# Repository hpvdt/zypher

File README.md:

# Zypher
Code and CAD of our 2019 ASME electronics system. Electronics hardware was designed in EAGLE, microcontroller code was prepared using the Arduino IDE. A mobile app prepared in MIT App Inventer 2 was used as the primary user interface.

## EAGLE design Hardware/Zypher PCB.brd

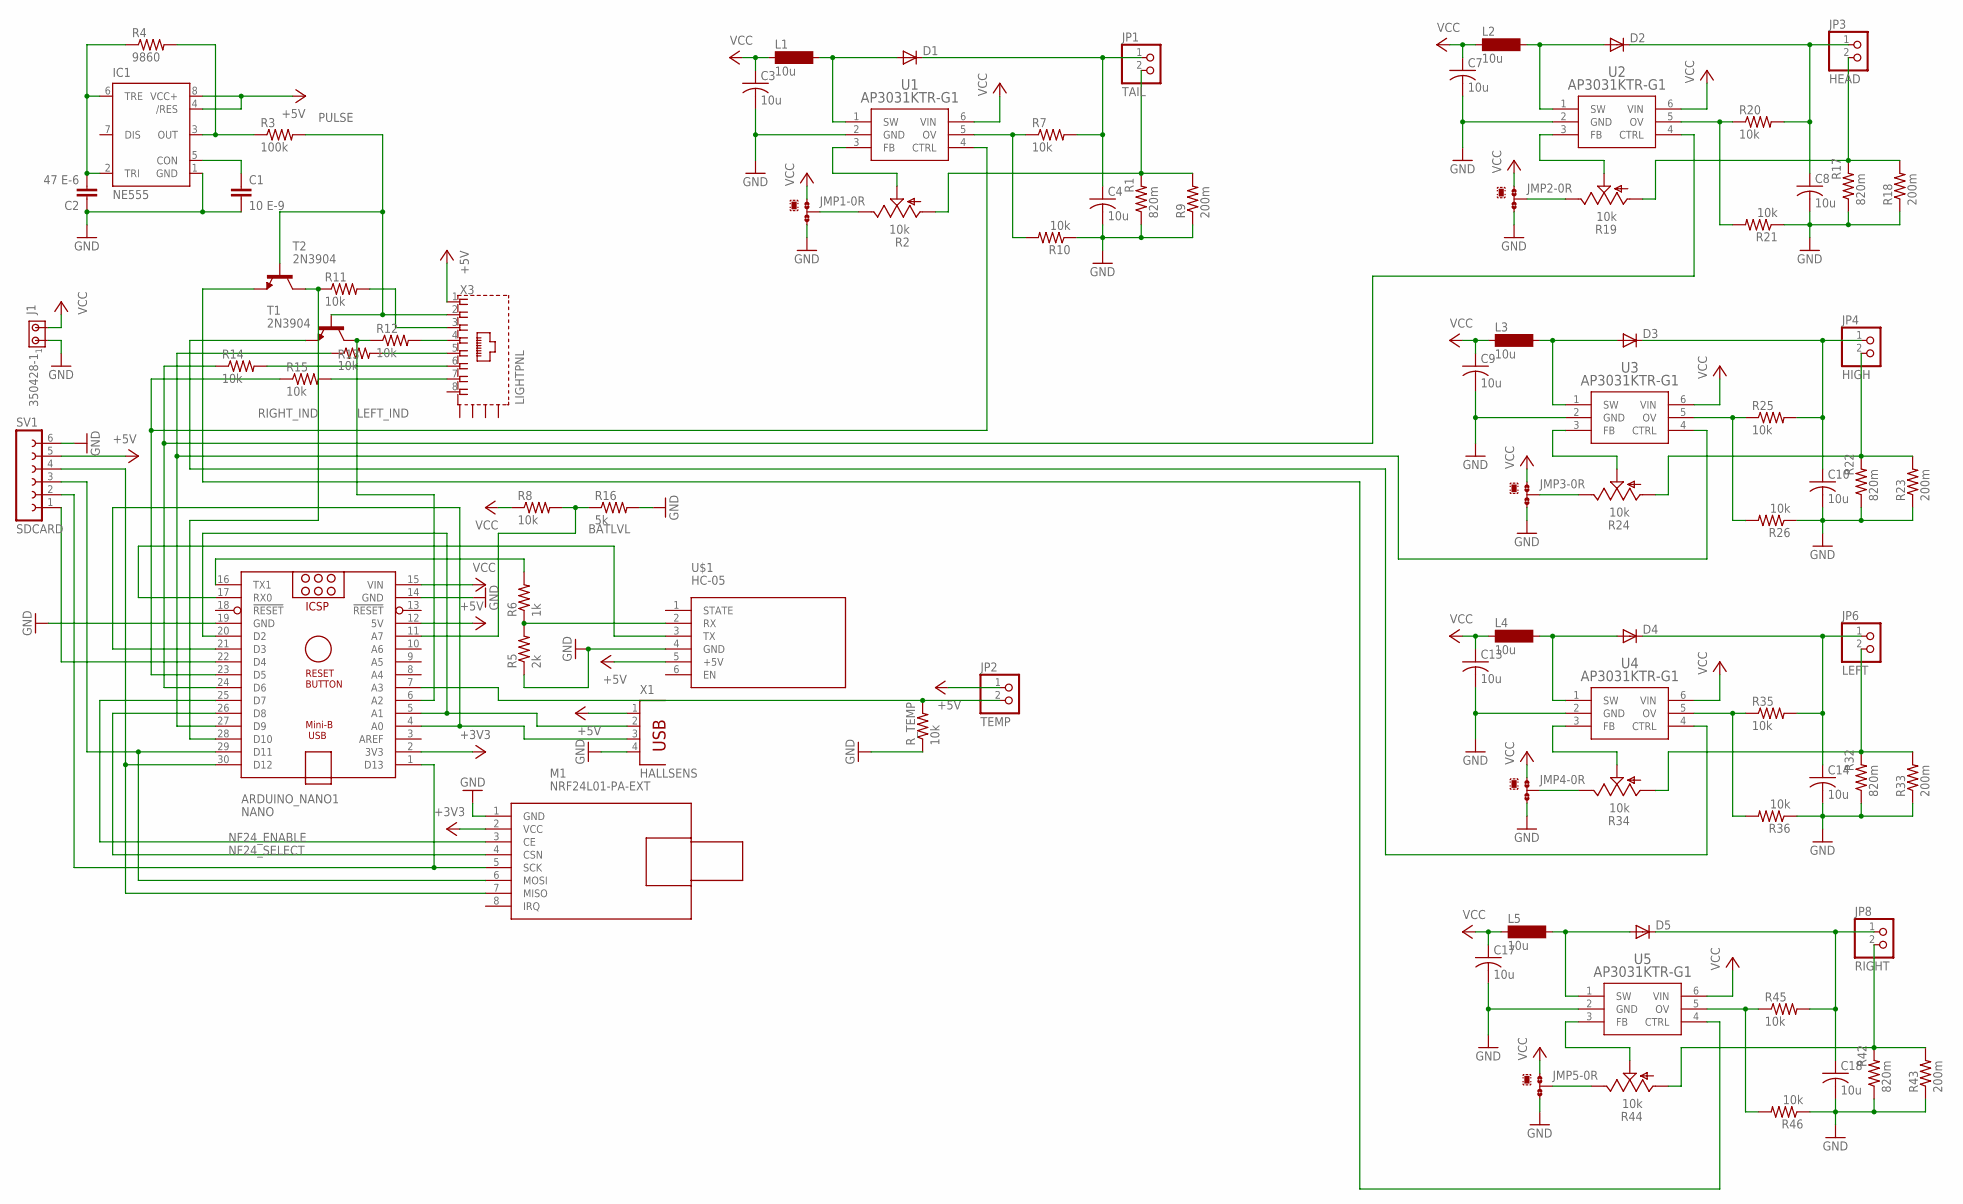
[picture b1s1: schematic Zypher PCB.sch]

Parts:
ARDUINO_NANO1: NANO; ARDUINO_NANO
C1: 10 E-9; C2.5-5
C2: 47 E-6; C2.5-5
C3, C4, C7, C8, C9, C10, C13, C14, C17, C18: 10u; C1206K
D1, D2, D3, D4, D5: DIODE-DO-214AC; DO-214AC
IC1: NE555; DIL-08
J1: 350428-1
JMP1, JMP2, JMP3, JMP4, JMP5: 0R-JUMPA; A0R-JMP
JP1: TAIL; 1X02
JP2: TEMP; 1X02
JP3: HEAD; 1X02
JP4: HIGH; 1X02
JP6: LEFT; 1X02
JP8: RIGHT; 1X02
L1, L2, L3, L4, L5: 10u; SD12K100
M1: NRF24L01-PA-EXT; WIRELESS-NRF24L01-PA-EXT
R1, R17, R22, R32, R42: 820m; R0603
R2, R19, R24, R34, R44: 10k; RJ9W
R3: 100k; 0207/7
R4: 9860; 0207/7
R5: 2k; 0204/7
R6: 1k; 0204/7
R7, R10, R20, R21, R25, R26, R35, R36, R45, R46: 10k; 0207/2V
R8, R11, R12, R13, R14, R15: 10k; 0207/7
R9, R18, R23, R33, R43: 200m; R0805
R16: 5k; 0207/7
R_TEMP: 10k; 0207/7
SV1: SDCARD; FE06W
T1, T2: 2N3904; TO92
U1, U2, U3, U4, U5: AP3031KTR-G1; SOT23-6
U$1: HC-05; WIRELESS-BLUETOOTH-HC-05
X1: HALLSENS; PN87520
X3: LIGHTPNL; RJ45-SHIELD1

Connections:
+3V3: ARDUINO_NANO1.2 (3V3), M1.2 (VCC)
+5V: ARDUINO_NANO1.12 (5V), IC1.4 (/RES), IC1.8 (VCC+), JP2.1, SV1.5, U$1.5 (+5V), X1.1, X3.1
BATLVL: ARDUINO_NANO1.11 (A7), R8.2, R16.1
CLK: ARDUINO_NANO1.1 (D13), M1.5 (SCK), SV1.2
GND: ARDUINO_NANO1.14 (GND), ARDUINO_NANO1.19 (GND), C1.2, C2.1, C3.2, C4.2, C7.2, C8.2, C9.2, C10.2, C13.2, C14.2, C17.2, C18.2, IC1.1 (GND), J1.1, JMP1.3, JMP2.3, JMP3.3, JMP4.3, JMP5.3, M1.1 (GND), R1.1, R5.1, R9.1, R10.1, R16.2, R17.1, R18.1, R21.1, R22.1, R23.1, R26.1, R32.1, R33.1, R36.1, R42.1, R43.1, R46.1, R_TEMP.1, SV1.6, U1.2 (GND), U2.2 (GND), U3.2 (GND), U4.2 (GND), U5.2 (GND), U$1.4 (GND), X1.4
HALL1: ARDUINO_NANO1.4 (A0), ARDUINO_NANO1.21 (D3), X1.3
HALL2: ARDUINO_NANO1.5 (A1), ARDUINO_NANO1.20 (D2), X1.2
HEAD_CTRL: ARDUINO_NANO1.24 (D6), R14.1, U2.4 (CTRL)
HIGH_CTRL: ARDUINO_NANO1.27 (D9), R13.1, U3.4 (CTRL)
LEFT+: C14.1, D4.C, JP6.1, R35.2
LEFT-: JP6.2, R32.2, R33.2, R34.A
LEFT_CTRL: T1.3 (E), U4.4 (CTRL)
LEFT_IND: ARDUINO_NANO1.6 (A2), R12.1, T1.1 (C)
MISO: ARDUINO_NANO1.30 (D12), M1.7 (MISO), SV1.4
MOSI: ARDUINO_NANO1.29 (D11), M1.6 (MOSI), SV1.3
unnamed: D1.A, L1.2, U1.1 (SW)
unnamed: C1.1, IC1.5 (CON)
unnamed: C4.1, D1.C, JP1.1, R7.2
unnamed: C2.2, IC1.2 (TRI), IC1.6 (TRE), R4.1
unnamed: IC1.3 (OUT), R3.1, R4.2
unnamed: R2.S, U1.3 (FB)
unnamed: JP1.2, R1.2, R2.A, R9.2
unnamed: JMP1.2, R2.E
unnamed: R5.2, R6.1, U$1.2 (RX)
unnamed: R7.1, R10.2, U1.5 (OV)
unnamed: R14.2, X3.6
unnamed: R13.2, X3.5
unnamed: R11.2, X3.3
unnamed: R12.2, X3.4
unnamed: R15.2, X3.7
unnamed: D2.A, L2.2, U2.1 (SW)
unnamed: C8.1, D2.C, JP3.1, R20.2
unnamed: JP3.2, R17.2, R18.2, R19.A
unnamed: R19.S, U2.3 (FB)
unnamed: JMP2.2, R19.E
unnamed: R20.1, R21.2, U2.5 (OV)
unnamed: D3.A, L3.2, U3.1 (SW)
unnamed: C10.1, D3.C, JP4.1, R25.2
unnamed: JP4.2, R22.2, R23.2, R24.A
unnamed: R24.S, U3.3 (FB)
unnamed: JMP3.2, R24.E
unnamed: R25.1, R26.2, U3.5 (OV)
unnamed: D4.A, L4.2, U4.1 (SW)
unnamed: R34.S, U4.3 (FB)
unnamed: JMP4.2, R34.E
unnamed: R35.1, R36.2, U4.5 (OV)
unnamed: D5.A, L5.2, U5.1 (SW)
unnamed: R44.S, U5.3 (FB)
unnamed: JMP5.2, R44.E
unnamed: R45.1, R46.2, U5.5 (OV)
NF24_ENABLE: ARDUINO_NANO1.25 (D7), M1.3 (CE)
NF24_SELECT: ARDUINO_NANO1.26 (D8), M1.4 (CSN)
PULSE: R3.2, T1.2 (B), T2.2 (B), X3.2
RIGHT+: C18.1, D5.C, JP8.1, R45.2
RIGHT-: JP8.2, R42.2, R43.2, R44.A
RIGHT_CTRL: T2.3 (E), U5.4 (CTRL)
RIGHT_IND: ARDUINO_NANO1.28 (D10), R11.1, T2.1 (C)
RX: ARDUINO_NANO1.17 (RX0), U$1.3 (TX)
SD_SEL: ARDUINO_NANO1.22 (D4), SV1.1
TAIL_CTRL: ARDUINO_NANO1.23 (D5), R15.1, U1.4 (CTRL)
TEMP: ARDUINO_NANO1.7 (A3), JP2.2, R_TEMP.2
TX: ARDUINO_NANO1.16 (TX1), R6.2
VCC: ARDUINO_NANO1.15 (VIN), C3.1, C7.1, C9.1, C13.1, C17.1, J1.2, JMP1.1, JMP2.1, JMP3.1, JMP4.1, JMP5.1, L1.1, L2.1, L3.1, L4.1, L5.1, R8.1, U1.6 (VIN), U2.6 (VIN), U3.6 (VIN), U4.6 (VIN), U5.6 (VIN)

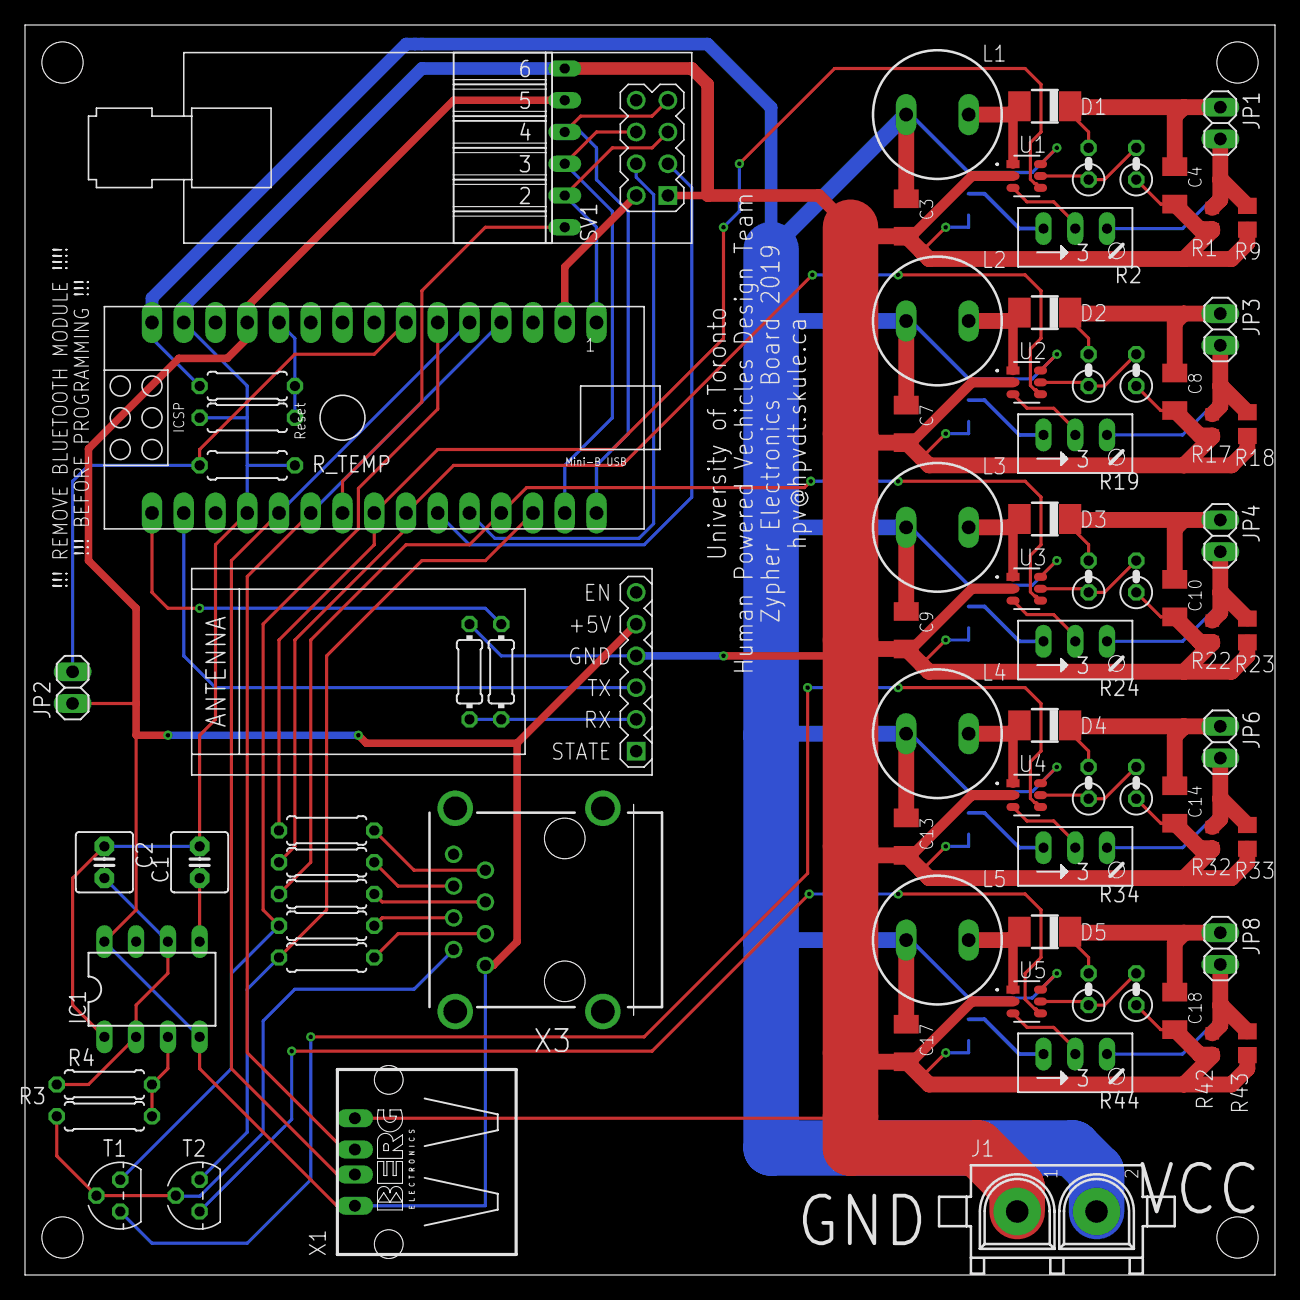
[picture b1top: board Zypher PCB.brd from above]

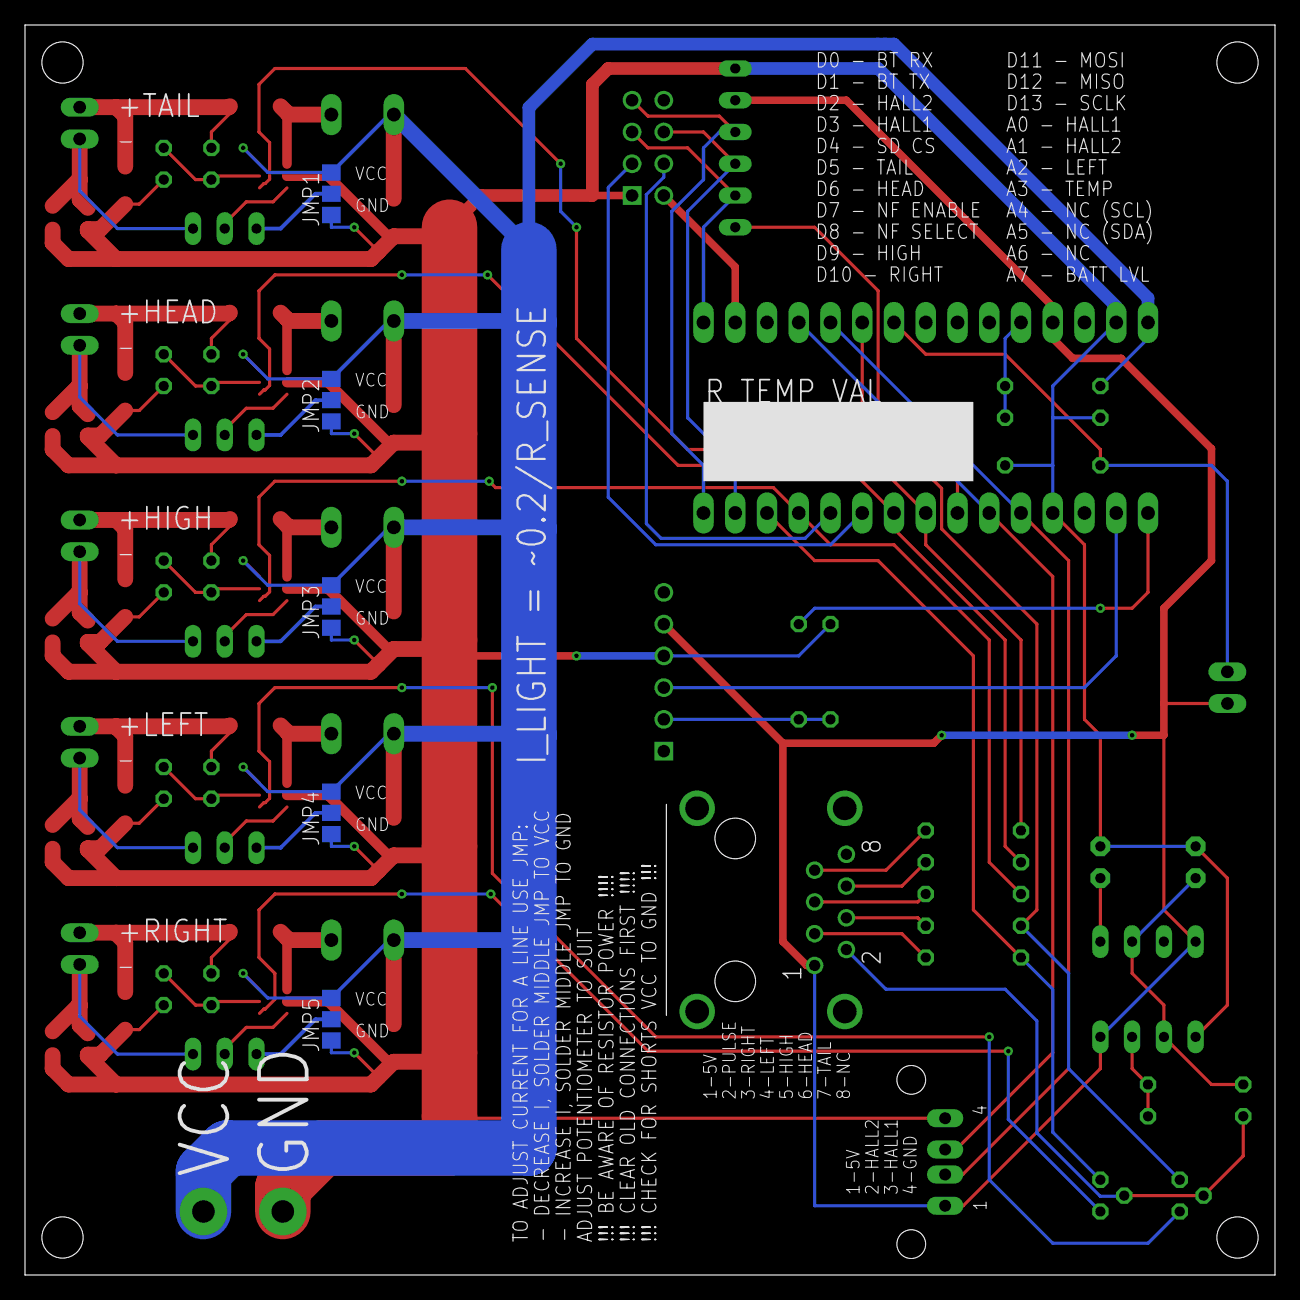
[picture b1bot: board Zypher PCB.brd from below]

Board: 2 copper layers, 100.0 x 100.0 mm, 85 parts (5 on the bottom side), 63 nets.

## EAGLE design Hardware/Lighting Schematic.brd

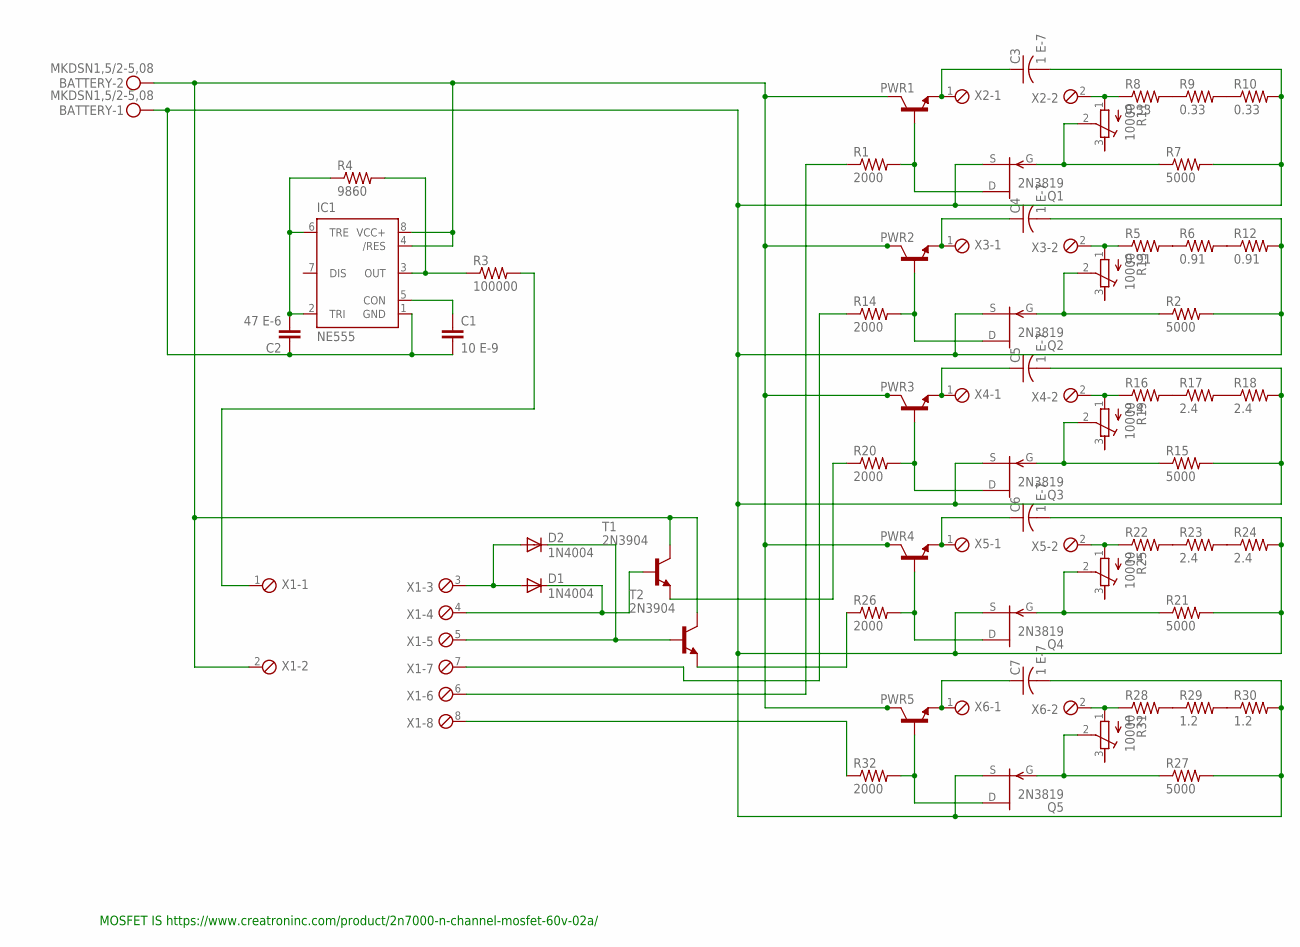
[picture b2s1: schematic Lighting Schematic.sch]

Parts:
BATTERY: MKDSN1,5/2-5,08
C1: 10 E-9; C2.5-5
C2: 47 E-6; C2.5-5
C3, C4, C5, C6, C7: 1 E-7; C075-052X106
D1, D2: 1N4004; DO41-10
IC1: NE555; DIL-08
PWR1, PWR2, PWR3, PWR4, PWR5: -NPN-TO220V; TO220V
Q1, Q2, Q3, Q4, Q5: 2N3819; TO92
R1, R14, R20, R26, R32: 2000; 0207/15
R2, R7, R15, R21, R27: 5000; 0207/10
R3: 100000; 0207/10
R4: 9860; 0207/10
R5, R6, R12: 0.91; P0817V
R8, R9, R10: 0.33; P0817V
R11, R13, R19, R25, R31: 10000; RTRIM3296W
R16, R17, R18, R22, R23, R24: 2.4; P0817V
R28, R29, R30: 1.2; P0817V
T1, T2: 2N3904; TO92
X1: MPT8; 8POL254
X2, X3, X4, X5, X6: MPT2; 2POL254

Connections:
GND: BATTERY.1, C1.2, C2.1, C3.2, C4.2, C5.2, C6.2, C7.2, IC1.1 (GND), Q1.3 (S), Q2.3 (S), Q3.3 (S), Q4.3 (S), Q5.3 (S), R2.2, R7.2, R10.2, R12.2, R15.2, R18.2, R21.2, R24.2, R27.2, R30.2
HEAD+: C4.1, PWR2.3 (E), X3.1
HEAD-: R5.1, R13.1 (A), X3.2
HIGH+: C3.1, PWR1.3 (E), X2.1
HIGH-: R8.1, R11.1 (A), X2.2
LEFT+: C5.1, PWR3.3 (E), X4.1
LEFT-: R16.1, R19.1 (A), X4.2
unnamed: R5.2, R6.1
unnamed: C1.1, IC1.5 (CON)
unnamed: R6.2, R12.1
unnamed: C2.2, IC1.2 (TRI), IC1.6 (TRE), R4.1
unnamed: IC1.3 (OUT), R3.1, R4.2
unnamed: D1.A, D2.A, X1.3
unnamed: D1.C, T1.2 (B), X1.4
unnamed: D2.C, T2.2 (B), X1.5
unnamed: R3.2, X1.1
unnamed: R8.2, R9.1
unnamed: R9.2, R10.1
unnamed: PWR1.1 (B), Q1.1 (D), R1.2
unnamed: Q1.2 (G), R7.1, R11.2 (S)
unnamed: PWR2.1 (B), Q2.1 (D), R14.2
unnamed: Q2.2 (G), R2.1, R13.2 (S)
unnamed: R1.1, X1.6
unnamed: R14.1, X1.7
unnamed: R26.1, T2.3 (E)
unnamed: R32.1, X1.8
unnamed: R16.2, R17.1
unnamed: R17.2, R18.1
unnamed: PWR3.1 (B), Q3.1 (D), R20.2
unnamed: Q3.2 (G), R15.1, R19.2 (S)
unnamed: R22.2, R23.1
unnamed: R23.2, R24.1
unnamed: PWR4.1 (B), Q4.1 (D), R26.2
unnamed: Q4.2 (G), R21.1, R25.2 (S)
unnamed: R28.2, R29.1
unnamed: R29.2, R30.1
unnamed: PWR5.1 (B), Q5.1 (D), R32.2
unnamed: Q5.2 (G), R27.1, R31.2 (S)
unnamed: R20.1, T1.3 (E)
RIGHT+: C6.1, PWR4.3 (E), X5.1
RIGHT-: R22.1, R25.1 (A), X5.2
TAIL+: C7.1, PWR5.3 (E), X6.1
TAIL-: R28.1, R31.1 (A), X6.2
VCC: BATTERY.2, IC1.4 (/RES), IC1.8 (VCC+), PWR1.2 (C), PWR2.2 (C), PWR3.2 (C), PWR4.2 (C), PWR5.2 (C), T1.1 (C), T2.1 (C), X1.2

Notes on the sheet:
MOSFET IS https://www.creatroninc.com/product/2n7000-n-channel-mosfet-60v-02a/

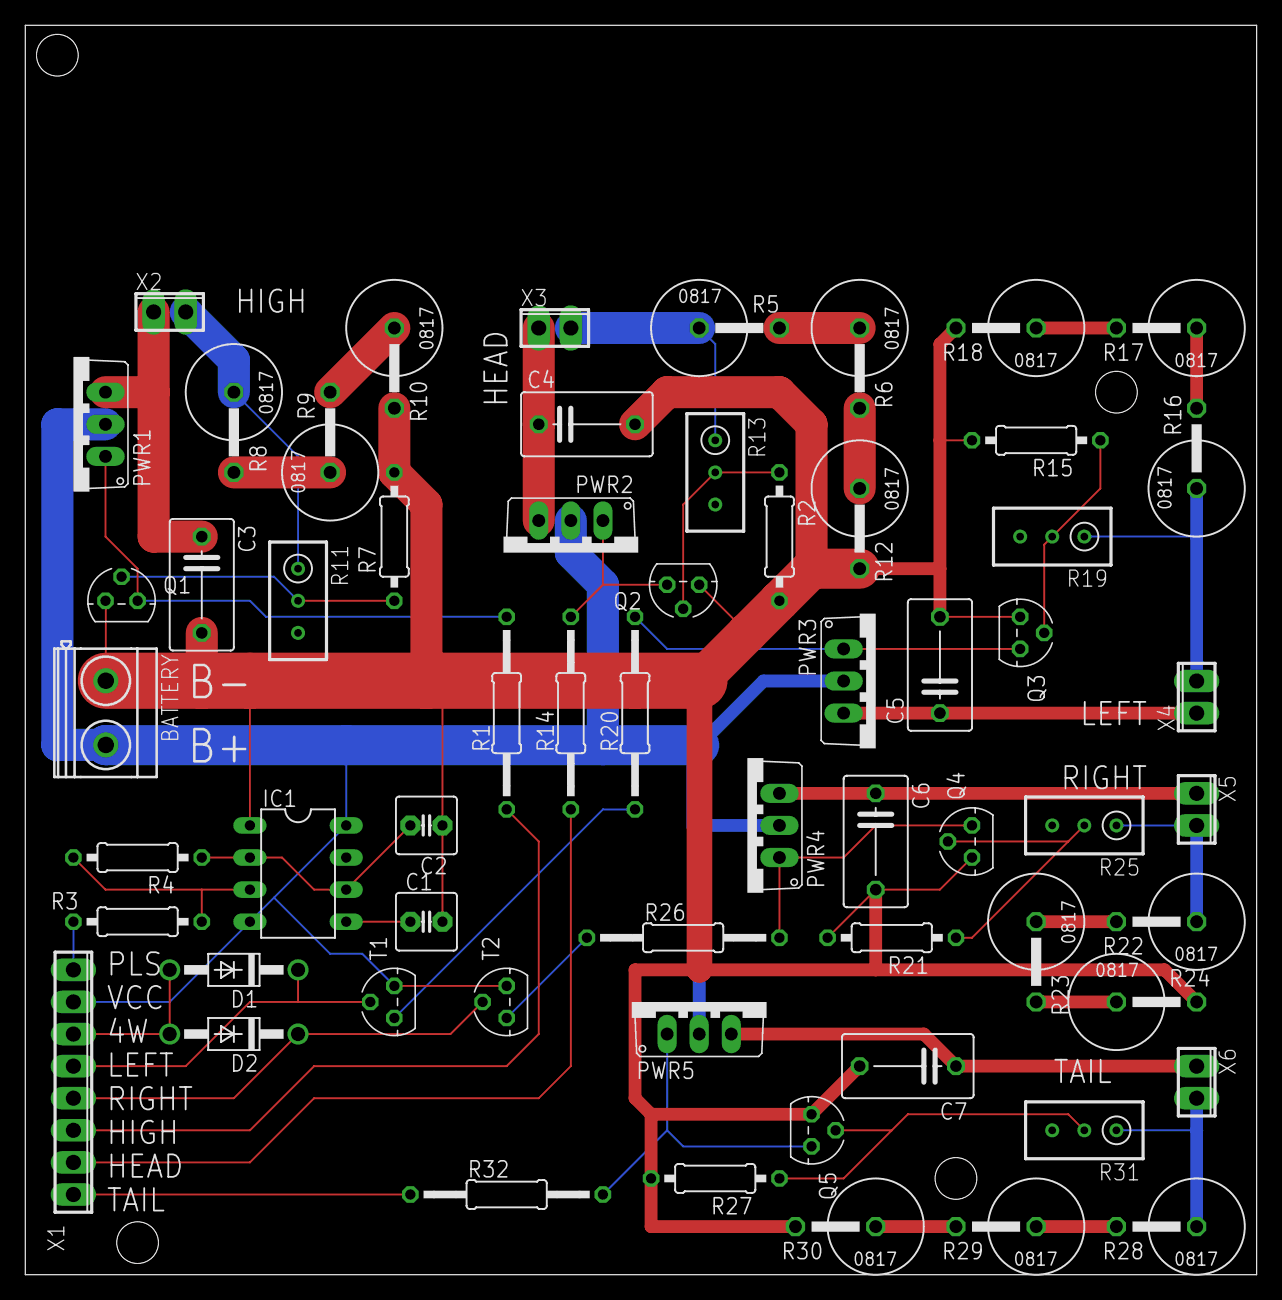
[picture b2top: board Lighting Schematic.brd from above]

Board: 2 copper layers, 97.5 x 98.9 mm, 61 parts (0 on the bottom side), 44 nets.

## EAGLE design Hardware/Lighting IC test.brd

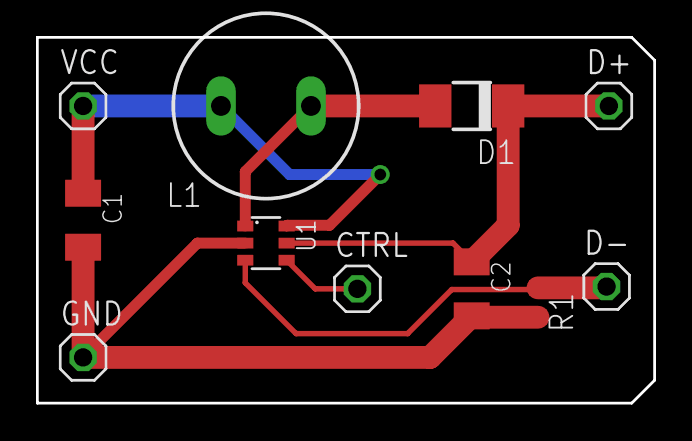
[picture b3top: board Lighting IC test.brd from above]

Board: 2 copper layers, 34.3 x 20.3 mm, 11 parts (0 on the bottom side), 6 nets.

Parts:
C1, C2: C1206K
CTRL: 1X01
D1: DO-214AC
D+: 1X01
D-: 1X01
GND: 1X01
L1: SD12K100
R1: R0603
U1: SOT23-6
VCC: 1X01

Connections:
CONTROL: CTRL.1, U1.4
FEEDBACK: D-.1, R1.1, U1.3
GND: C1.2, C2.2, GND.1, R1.2, U1.2
SWITCH: D1.A, L1.1, U1.1
VCC: C1.1, L1.2, U1.6, VCC.1
VOUT: C2.1, D1.C, D+.1, U1.5

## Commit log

2019-11-08 Initial commit
    Upload of the files used.
2021-06-07 Upload of Zypher files

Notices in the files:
parts and their libraries:
diy-modules: Released under the Creative Commons Attribution 4.0 International License: http://creativecommons.org/licenses/by/4.0
